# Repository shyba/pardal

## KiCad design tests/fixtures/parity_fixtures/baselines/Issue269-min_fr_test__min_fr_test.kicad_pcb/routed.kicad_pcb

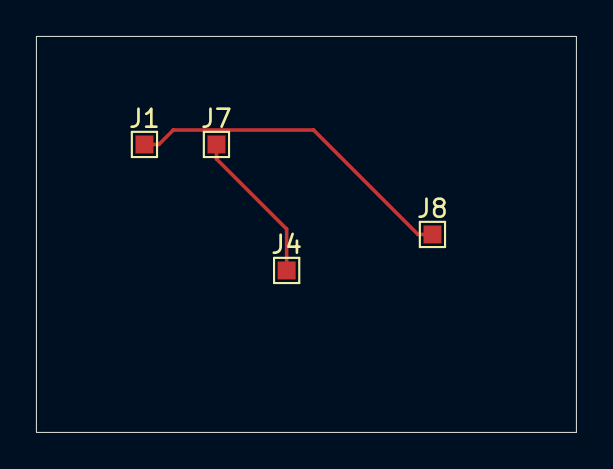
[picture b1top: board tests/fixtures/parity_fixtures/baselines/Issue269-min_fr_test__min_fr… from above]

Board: 4 copper layers, 30.0 x 22.0 mm, 4 parts (0 on the bottom side), 2 nets.

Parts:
J1, J4, J7, J8: Conn_01x01_Pin; TestPoint_Pad_1.0x1.0mm

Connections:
GND: J4.1, J7.1
unnamed: J1.1, J8.1

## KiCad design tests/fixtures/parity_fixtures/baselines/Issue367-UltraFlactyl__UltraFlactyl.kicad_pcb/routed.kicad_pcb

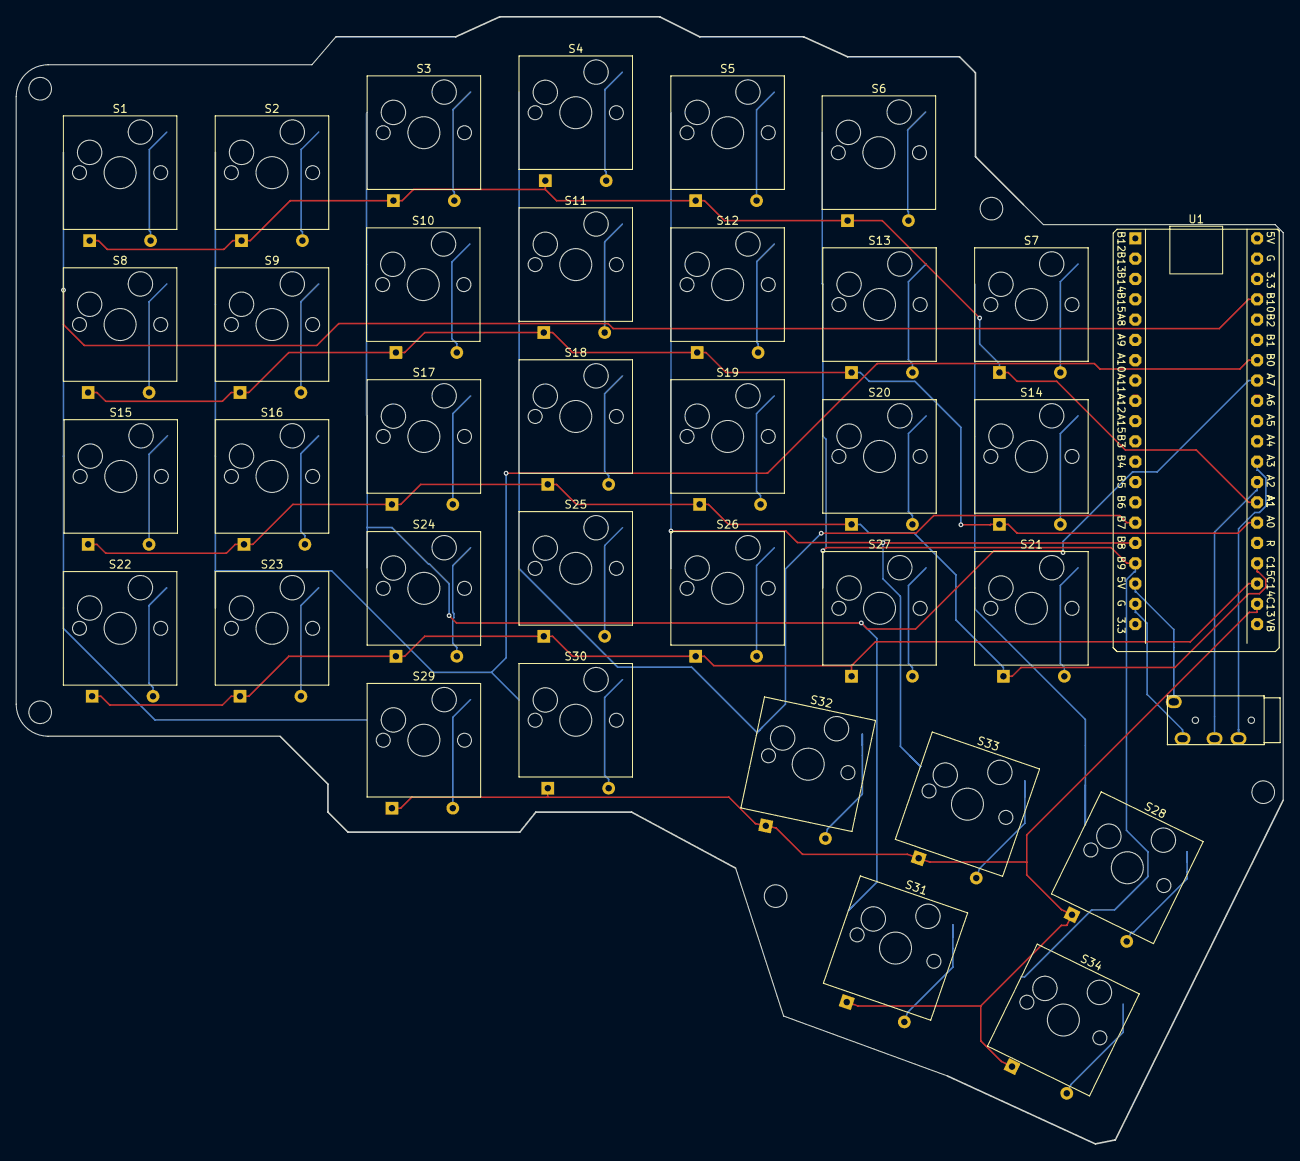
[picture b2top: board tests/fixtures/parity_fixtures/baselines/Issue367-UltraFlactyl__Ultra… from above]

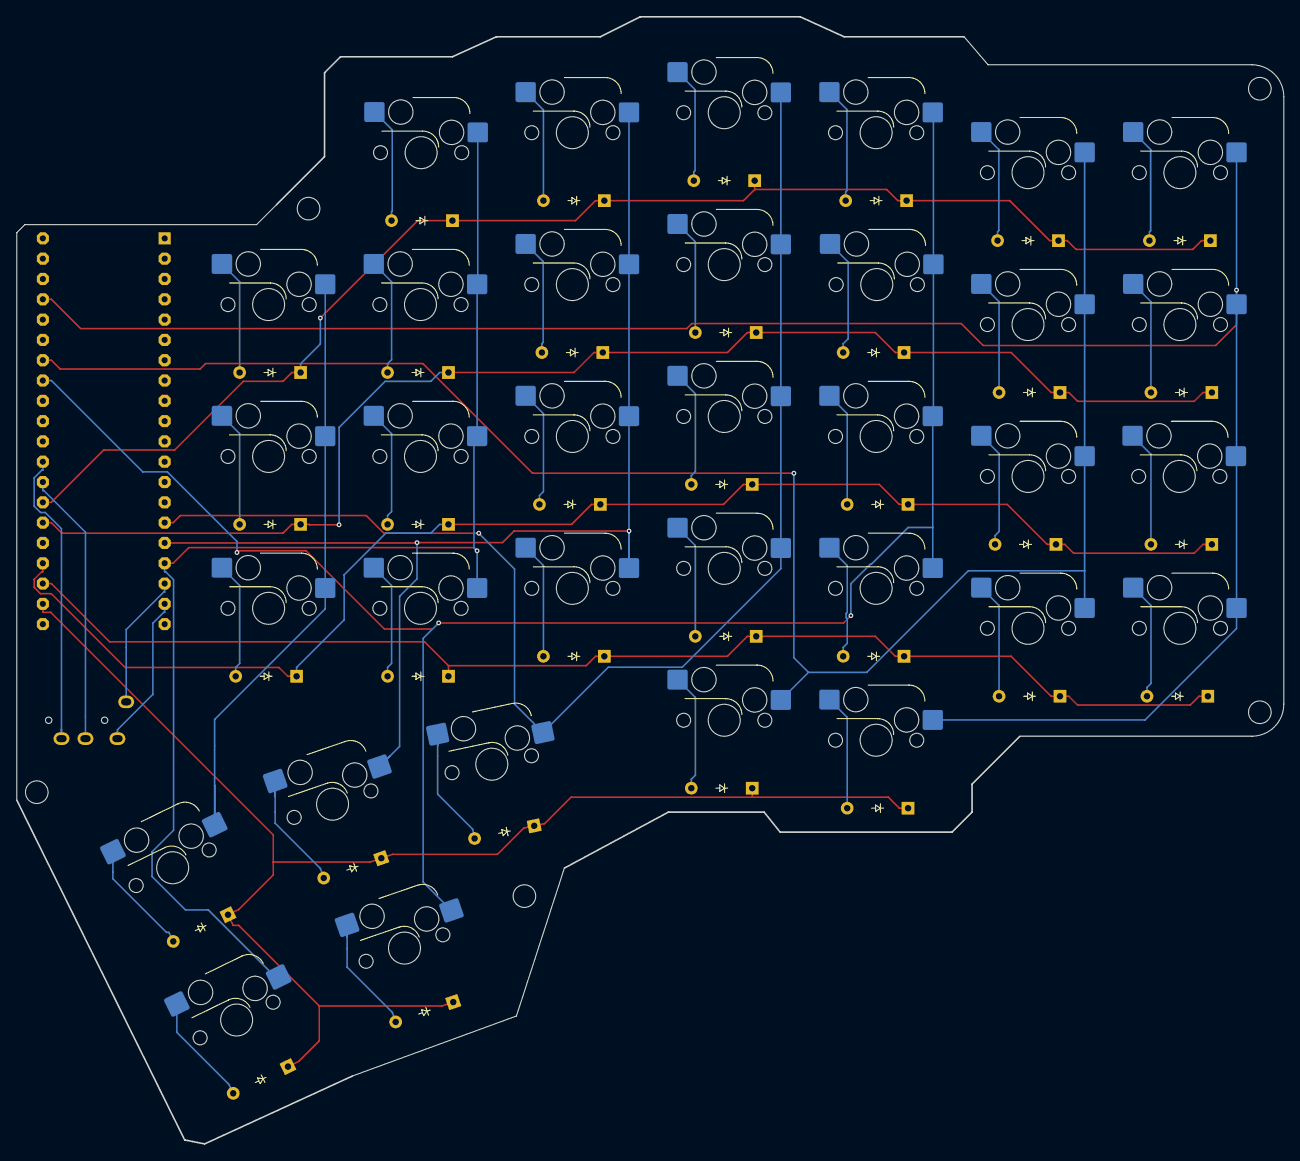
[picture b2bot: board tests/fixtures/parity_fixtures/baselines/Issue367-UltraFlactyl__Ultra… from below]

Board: 2 copper layers, 158.5 x 141.0 mm, 70 parts (34 on the bottom side), 50 nets.

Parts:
D1, D2, D3, D4, D5, D6, D7, D8, D9, D10, D11, D12, D13, D14, D15, D16, D17, D18, D19, D20, D21, D22, D23, D24, D25, D26, D27, D28, D29, D30, D31, D32, D33, D34: Diode; Diode_DO-35
S1, S2, S3, S4, S5, S6, S7, S8, S9, S10, S11, S12, S13, S14, S15, S16, S17, S18, S19, S20, S21, S22, S23, S24, S25, S26, S27, S28, S29, S30, S31, S32, S33, S34: Keyswitch; Hotswap_MX_1.00u
U1: STM32F411 BlackPill; STM32F411_Black_Pill
U2: TRRS; TRRS_PJ-320A

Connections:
C1: S1.1, S8.1, S15.1, S22.1, S29.1, U1.37 (B10)
C2: S2.1, S9.1, S16.1, S23.1, S30.1, U1.34 (B0)
C3: S3.1, S10.1, S17.1, S24.1, S31.1, U1.33 (A7)
C4: S4.1, S11.1, S18.1, S25.1, S32.1, U1.15 (B7)
C5: S5.1, S12.1, S19.1, S26.1, S33.1, U1.16 (B8)
C6: S6.1, S13.1, S20.1, S27.1, S34.1, U1.17 (B9)
C7: S7.1, S14.1, S21.1, S28.1
GND: U1.19 (G), U2.2 (TIP)
unnamed: D1.2 (A), S1.2
unnamed: D2.2 (A), S2.2
unnamed: D3.2 (A), S3.2
unnamed: D4.2 (A), S4.2
unnamed: D5.2 (A), S5.2
unnamed: D6.2 (A), S6.2
unnamed: D7.2 (A), S7.2
unnamed: D8.2 (A), S8.2
unnamed: D9.2 (A), S9.2
unnamed: D10.2 (A), S10.2
unnamed: D11.2 (A), S11.2
unnamed: D12.2 (A), S12.2
unnamed: D13.2 (A), S13.2
unnamed: D14.2 (A), S14.2
unnamed: D15.2 (A), S15.2
unnamed: D16.2 (A), S16.2
unnamed: D17.2 (A), S17.2
unnamed: D18.2 (A), S18.2
unnamed: D19.2 (A), S19.2
unnamed: D20.2 (A), S20.2
unnamed: D21.2 (A), S21.2
unnamed: D22.2 (A), S22.2
unnamed: D23.2 (A), S23.2
unnamed: D24.2 (A), S24.2
unnamed: D25.2 (A), S25.2
unnamed: D26.2 (A), S26.2
unnamed: D27.2 (A), S27.2
unnamed: D28.2 (A), S28.2
unnamed: D29.2 (A), S29.2
unnamed: D30.2 (A), S30.2
unnamed: D31.2 (A), S31.2
unnamed: D32.2 (A), S32.2
unnamed: D33.2 (A), S33.2
unnamed: D34.2 (A), S34.2
R1: D1.1 (K), D2.1 (K), D3.1 (K), D4.1 (K), D5.1 (K), D6.1 (K), D7.1 (K), U1.27 (A1)
R2: D8.1 (K), D9.1 (K), D10.1 (K), D11.1 (K), D12.1 (K), D13.1 (K), D14.1 (K), U1.26 (A0)
R3: D15.1 (K), D16.1 (K), D17.1 (K), D18.1 (K), D19.1 (K), D20.1 (K), D21.1 (K), U1.24 (C15)
R4: D22.1 (K), D23.1 (K), D24.1 (K), D25.1 (K), D26.1 (K), D27.1 (K), U1.23 (C14)
R5: D28.1 (K), D29.1 (K), D30.1 (K), D31.1 (K), D32.1 (K), D33.1 (K), D34.1 (K), U1.22 (C13)
RX: U1.28 (A2), U2.3 (RING1)
TX: U1.29 (A3), U2.4 (RING2)
VCC: U1.18 (5V), U2.1 (SLEEVE)
